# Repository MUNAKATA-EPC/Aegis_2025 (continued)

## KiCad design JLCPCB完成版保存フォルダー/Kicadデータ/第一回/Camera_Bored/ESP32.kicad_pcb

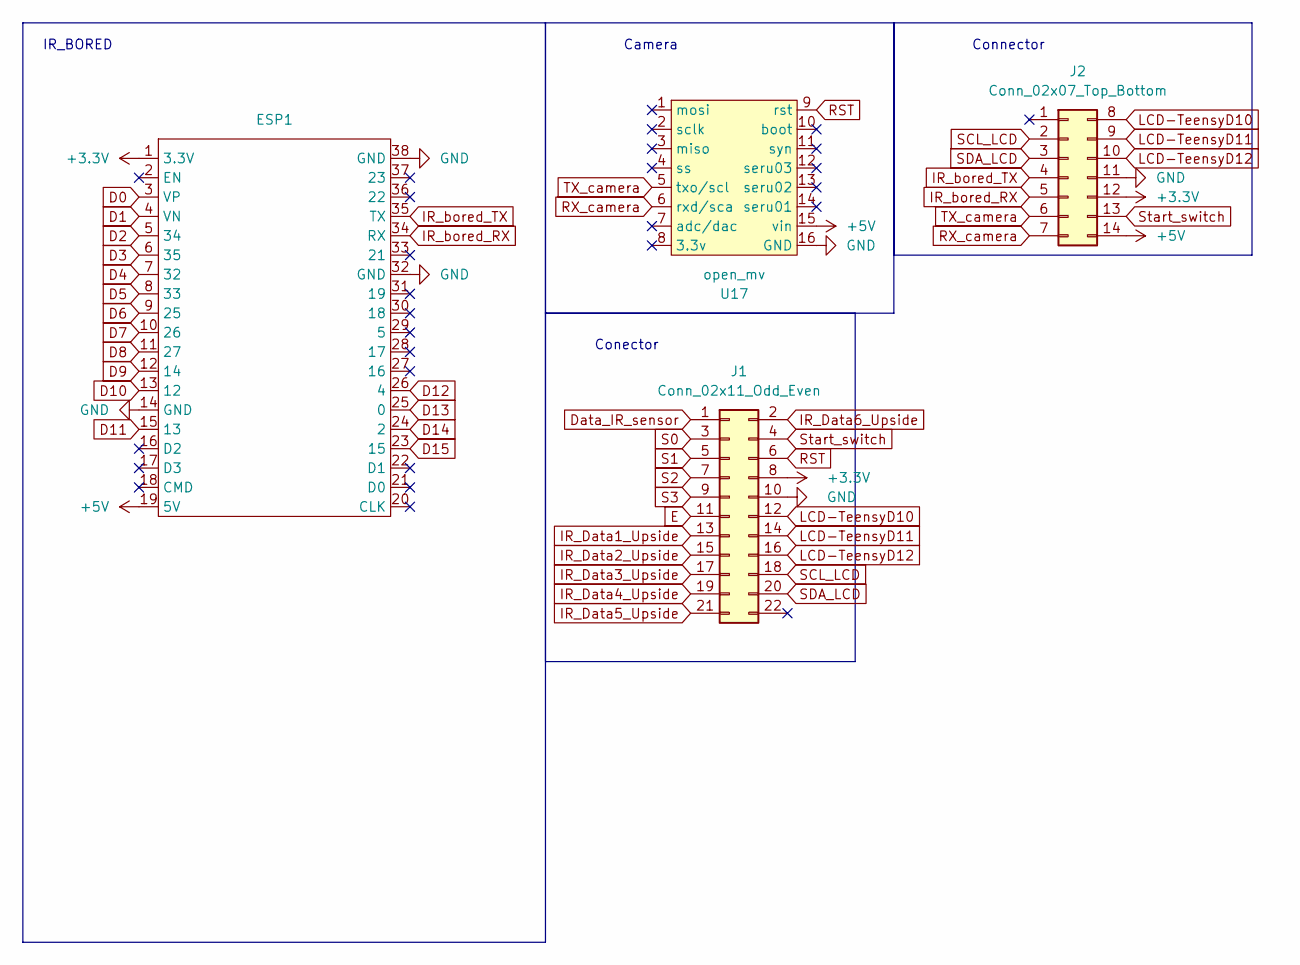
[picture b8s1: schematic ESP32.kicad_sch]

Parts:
ESP1: ESP32-DevKitC
J1: Conn_02x11_Odd_Even; PinHeader_2x11_P2.54mm_Vertical
J2: Conn_02x07_Top_Bottom; IDC-Header_2x07_P2.54mm_Vertical
U17: open_mv; OpenMV

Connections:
+3.3V: ESP1.1 (3.3V), J1.8, J2.12
+5V: ESP1.19 (5V), J2.14, U17.15 (vin)
D0: ESP1.3 (VP)
D1: ESP1.4 (VN)
D2: ESP1.5 (34)
D3: ESP1.6 (35)
D4: ESP1.7 (32)
D5: ESP1.8 (33)
D6: ESP1.9 (25)
D7: ESP1.10 (26)
D8: ESP1.11 (27)
D9: ESP1.12 (14)
D10: ESP1.13 (12)
D11: ESP1.15 (13)
D12: ESP1.26 (4)
D13: ESP1.25 (0)
D14: ESP1.24 (2)
D15: ESP1.23 (15)
Data_IR_sensor: J1.1
E: J1.11
GND: ESP1.14 (GND), ESP1.32 (GND), ESP1.38 (GND), J1.10, J2.11, U17.16 (GND)
IR_Data1_Upside: J1.13
IR_Data2_Upside: J1.15
IR_Data3_Upside: J1.17
IR_Data4_Upside: J1.19
IR_Data5_Upside: J1.21
IR_Data6_Upside: J1.2
IR_bored_RX: ESP1.34 (RX), J2.5
IR_bored_TX: ESP1.35 (TX), J2.4
LCD-TeensyD10: J1.12, J2.8
LCD-TeensyD11: J1.14, J2.9
LCD-TeensyD12: J1.16, J2.10
RST: J1.6, U17.9 (rst)
RX_camera: J2.7, U17.6 (rxd/sca)
S0: J1.3
S1: J1.5
S2: J1.7
S3: J1.9
SCL_LCD: J1.18, J2.2
SDA_LCD: J1.20, J2.3
Start_switch: J1.4, J2.13
TX_camera: J2.6, U17.5 (txo/scl)

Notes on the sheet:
Connector
Conector
IR_BORED
Camera

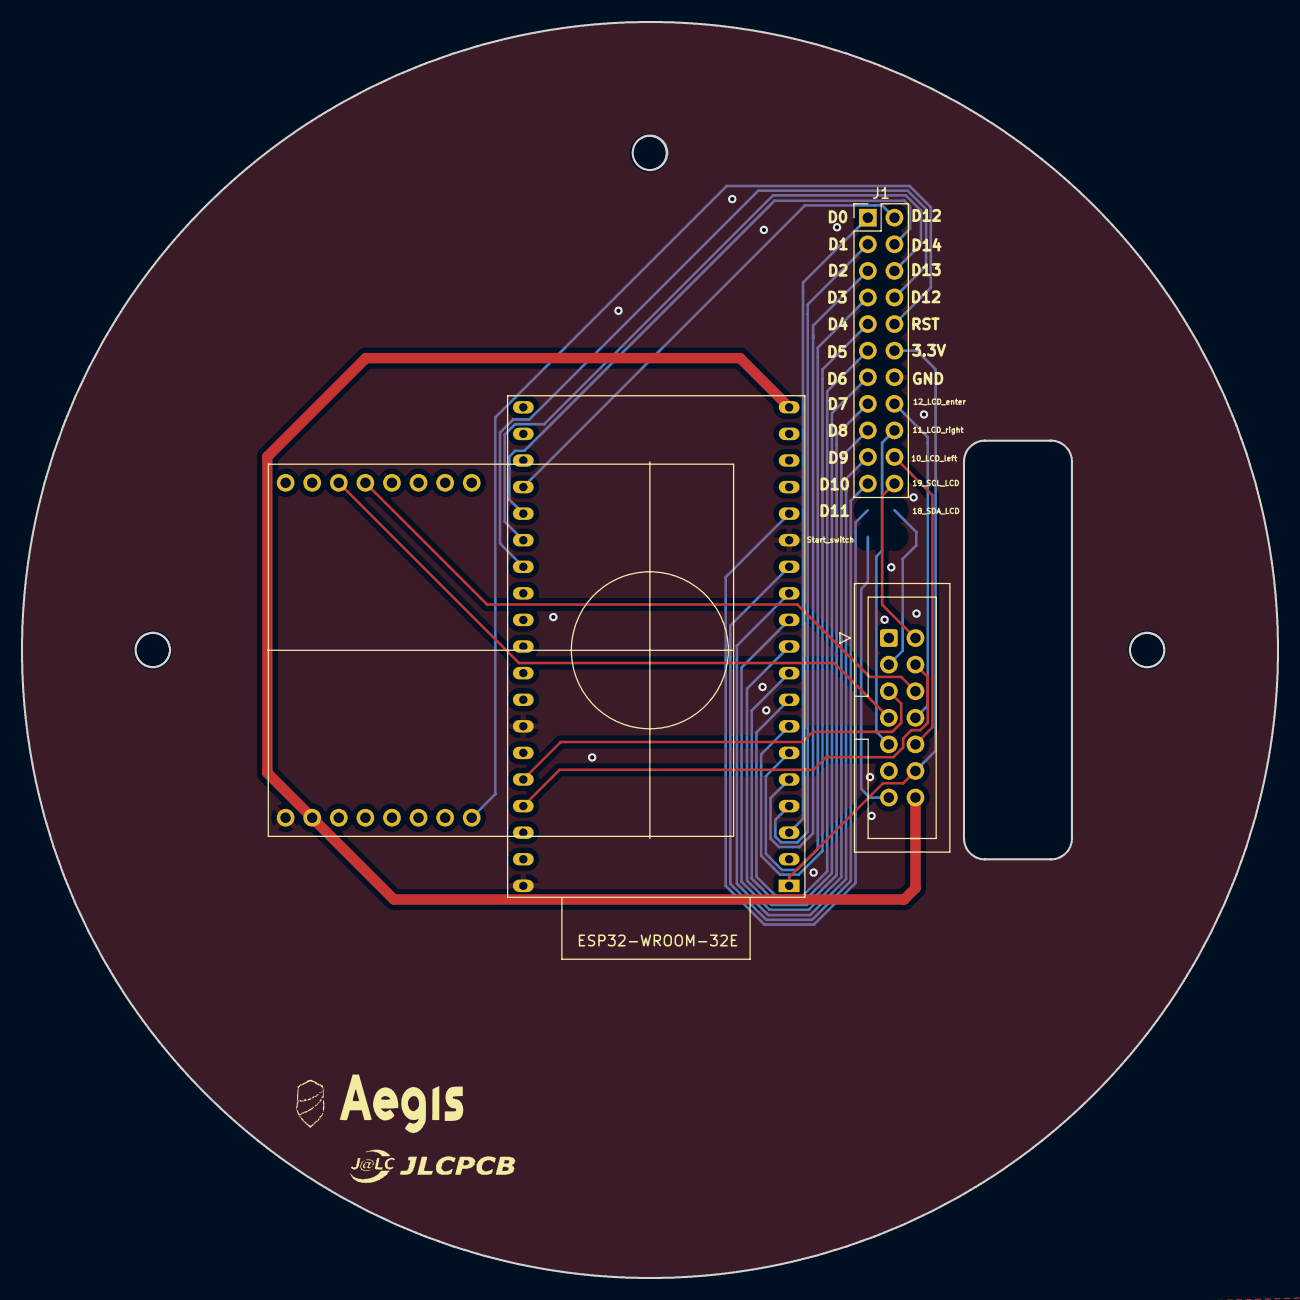
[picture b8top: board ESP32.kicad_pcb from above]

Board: 2 copper layers, 120.0 x 120.0 mm, 4 parts (0 on the bottom side), 14 nets.

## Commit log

2024-04-15 イージステスト
    適当
2024-06-27 aa
    aa
2024-07-14 かえました
2025-06-26 Create 2025_全国_goal_keeper
    ooo
2025-06-26 Delete 2025_全国_goal_keeper
    miss
2025-06-26 Create 2025_全国_goal_keeper
2025-06-26 Create a
2025-06-26 Create aaaa
2025-06-26 Create defence_IR_seeeduino
2025-06-26 Create fakkajka
2025-06-26 aaaaaa
2025-06-26 Create Kicad
2025-06-26 Create 2024_japan_open_キリン
2025-06-26 英語
    英語にしたよ
2025-06-26 Create
2025-06-26 英語
    英語に変えた
2025-06-26 kaeta
    kaeta
2025-06-26 add files
2025-06-26 namaekaeta
    yayyayay
2025-06-26 更新しました。
2025-06-28 寝よう！！
2025-06-28 基板データ
2025-06-28 クラファン
2025-06-28 イージスデータ
2025-06-28 プレゼンシート
    英語訳
2025-06-30 英語版
    訂正用
2025-06-30 camera
    カーペット用に変えました
2025-07-01 英語版
    コスト追加
2025-07-01 英語版
    カメラ
2025-07-01 tanomu
2025-07-01 camera
    あとカメラをカーペットから変更した。取材のインサート用
2025-07-01 加速度翻訳
    2回目
2025-07-01 移動平均終わり
2025-07-02 camera
2025-07-02 LINEのファイルを変えた
2025-07-02 フォルダ変更
2025-07-02 IRnoファイルがおかしい
2025-07-02 aaaa
2025-07-02 pure
2025-07-02 e英語版
    訂正
2025-07-03 imadakouji
2025-07-03 imadakou
2025-07-03 Method/Production/Design final
    多分完成
2025-07-03 hennkou
2025-07-05 line基板
    追加しました
2025-07-05 gannbatta
2025-07-06 yatta
    プログラむ変えました
2025-07-06 gannbaro-
2025-07-06 プレゼンシート
    修正済み
2025-07-07 qaaa
2025-07-07 あと少し
2025-07-07 linenominoyatu kansei
2025-07-08 flowchartを上げました。
    写真も載せないとーー
2025-07-08 忘れ物０で行こう!!
2025-07-08 完成ほぼ
2025-07-09 sukusyo
2025-07-09 poster
2025-07-09 syasin
2025-07-09 Create About Hardware
2025-07-09 Create design
2025-07-09 Create de
2025-07-09 TDP link
2025-07-09 TDP用ファイルアップロード
2025-07-09 motimono
2025-07-09 持ち物リスト完了
2025-07-10 プログラム合わせた
2025-07-10 プレゼンシート
    太文字完成
2025-07-10 英語版
    修正
2025-07-10 kannsei
2025-07-10 持ち物リスト完成
2025-07-11 aaaaaaaa
2025-07-11 Camera
    修正
2025-07-12 purezennsi-tokannsei
2025-07-12 aaaaaaaaaa
2025-07-16 isihara
2025-07-16 sasa
2025-07-16 kousinn
2025-07-16 anime-tion
2025-07-16 プレゼン
    変更
2025-07-16 sakousinn
2025-07-16 presen
    Hardware
2025-07-16 syuusei
    syusei
2025-07-17 大会初日 アタッカー
2025-07-18 二日目頑張ろう！！！
2025-07-19 世界優勝!!!頑張ろう！
2026-04-10 ははははは
2026-04-14 kannsei
    a
